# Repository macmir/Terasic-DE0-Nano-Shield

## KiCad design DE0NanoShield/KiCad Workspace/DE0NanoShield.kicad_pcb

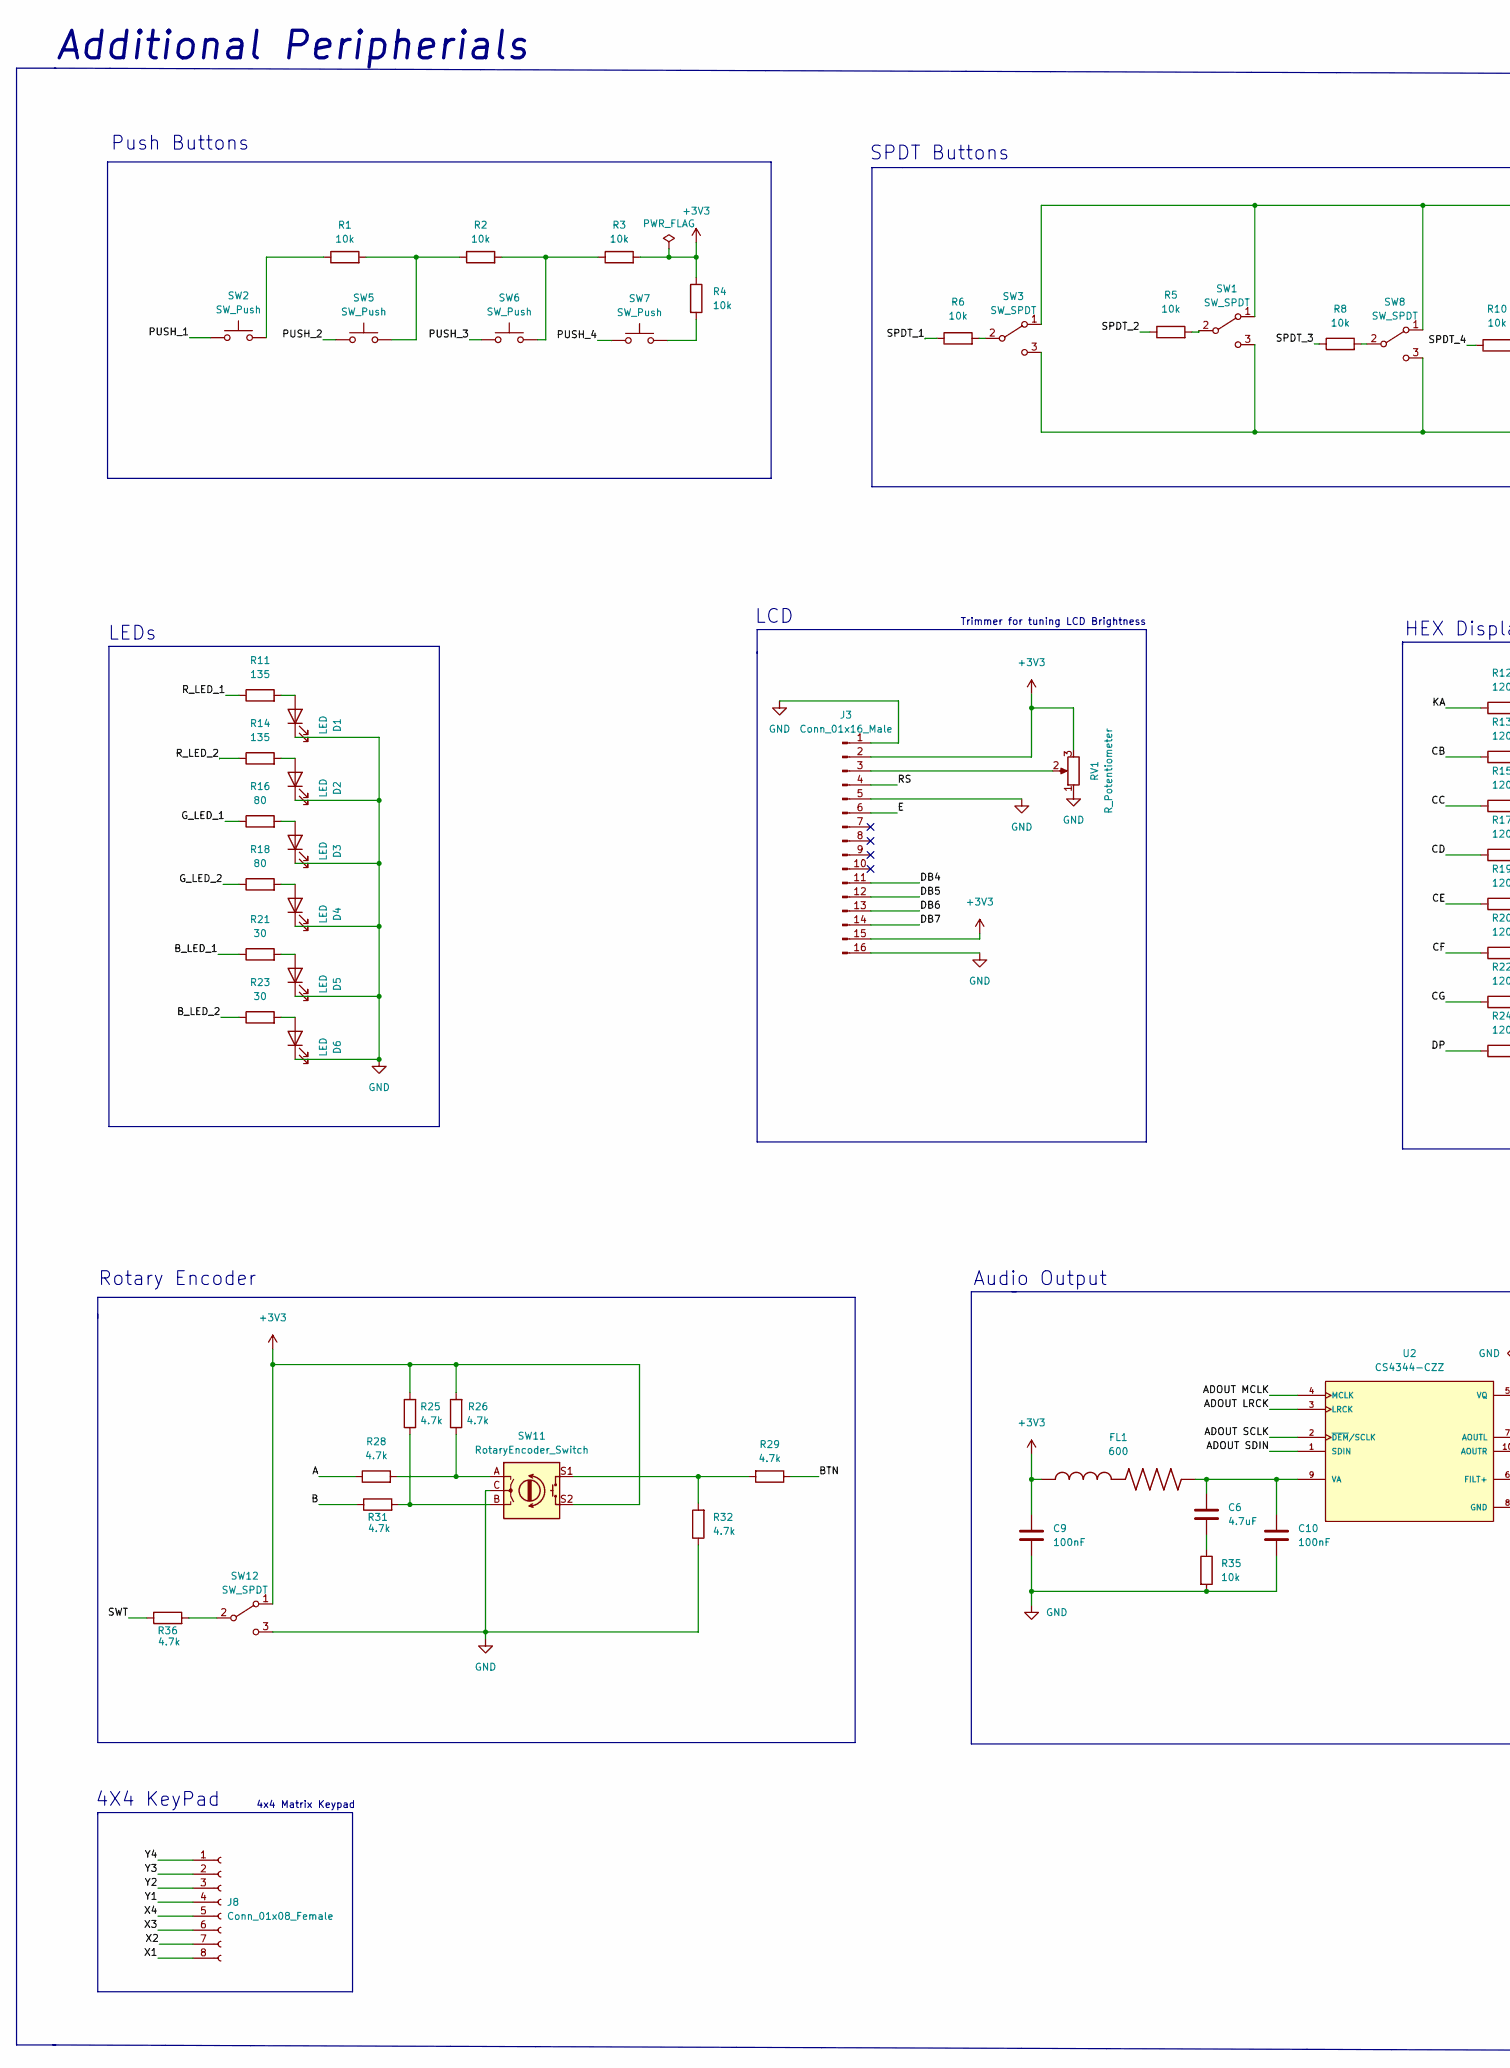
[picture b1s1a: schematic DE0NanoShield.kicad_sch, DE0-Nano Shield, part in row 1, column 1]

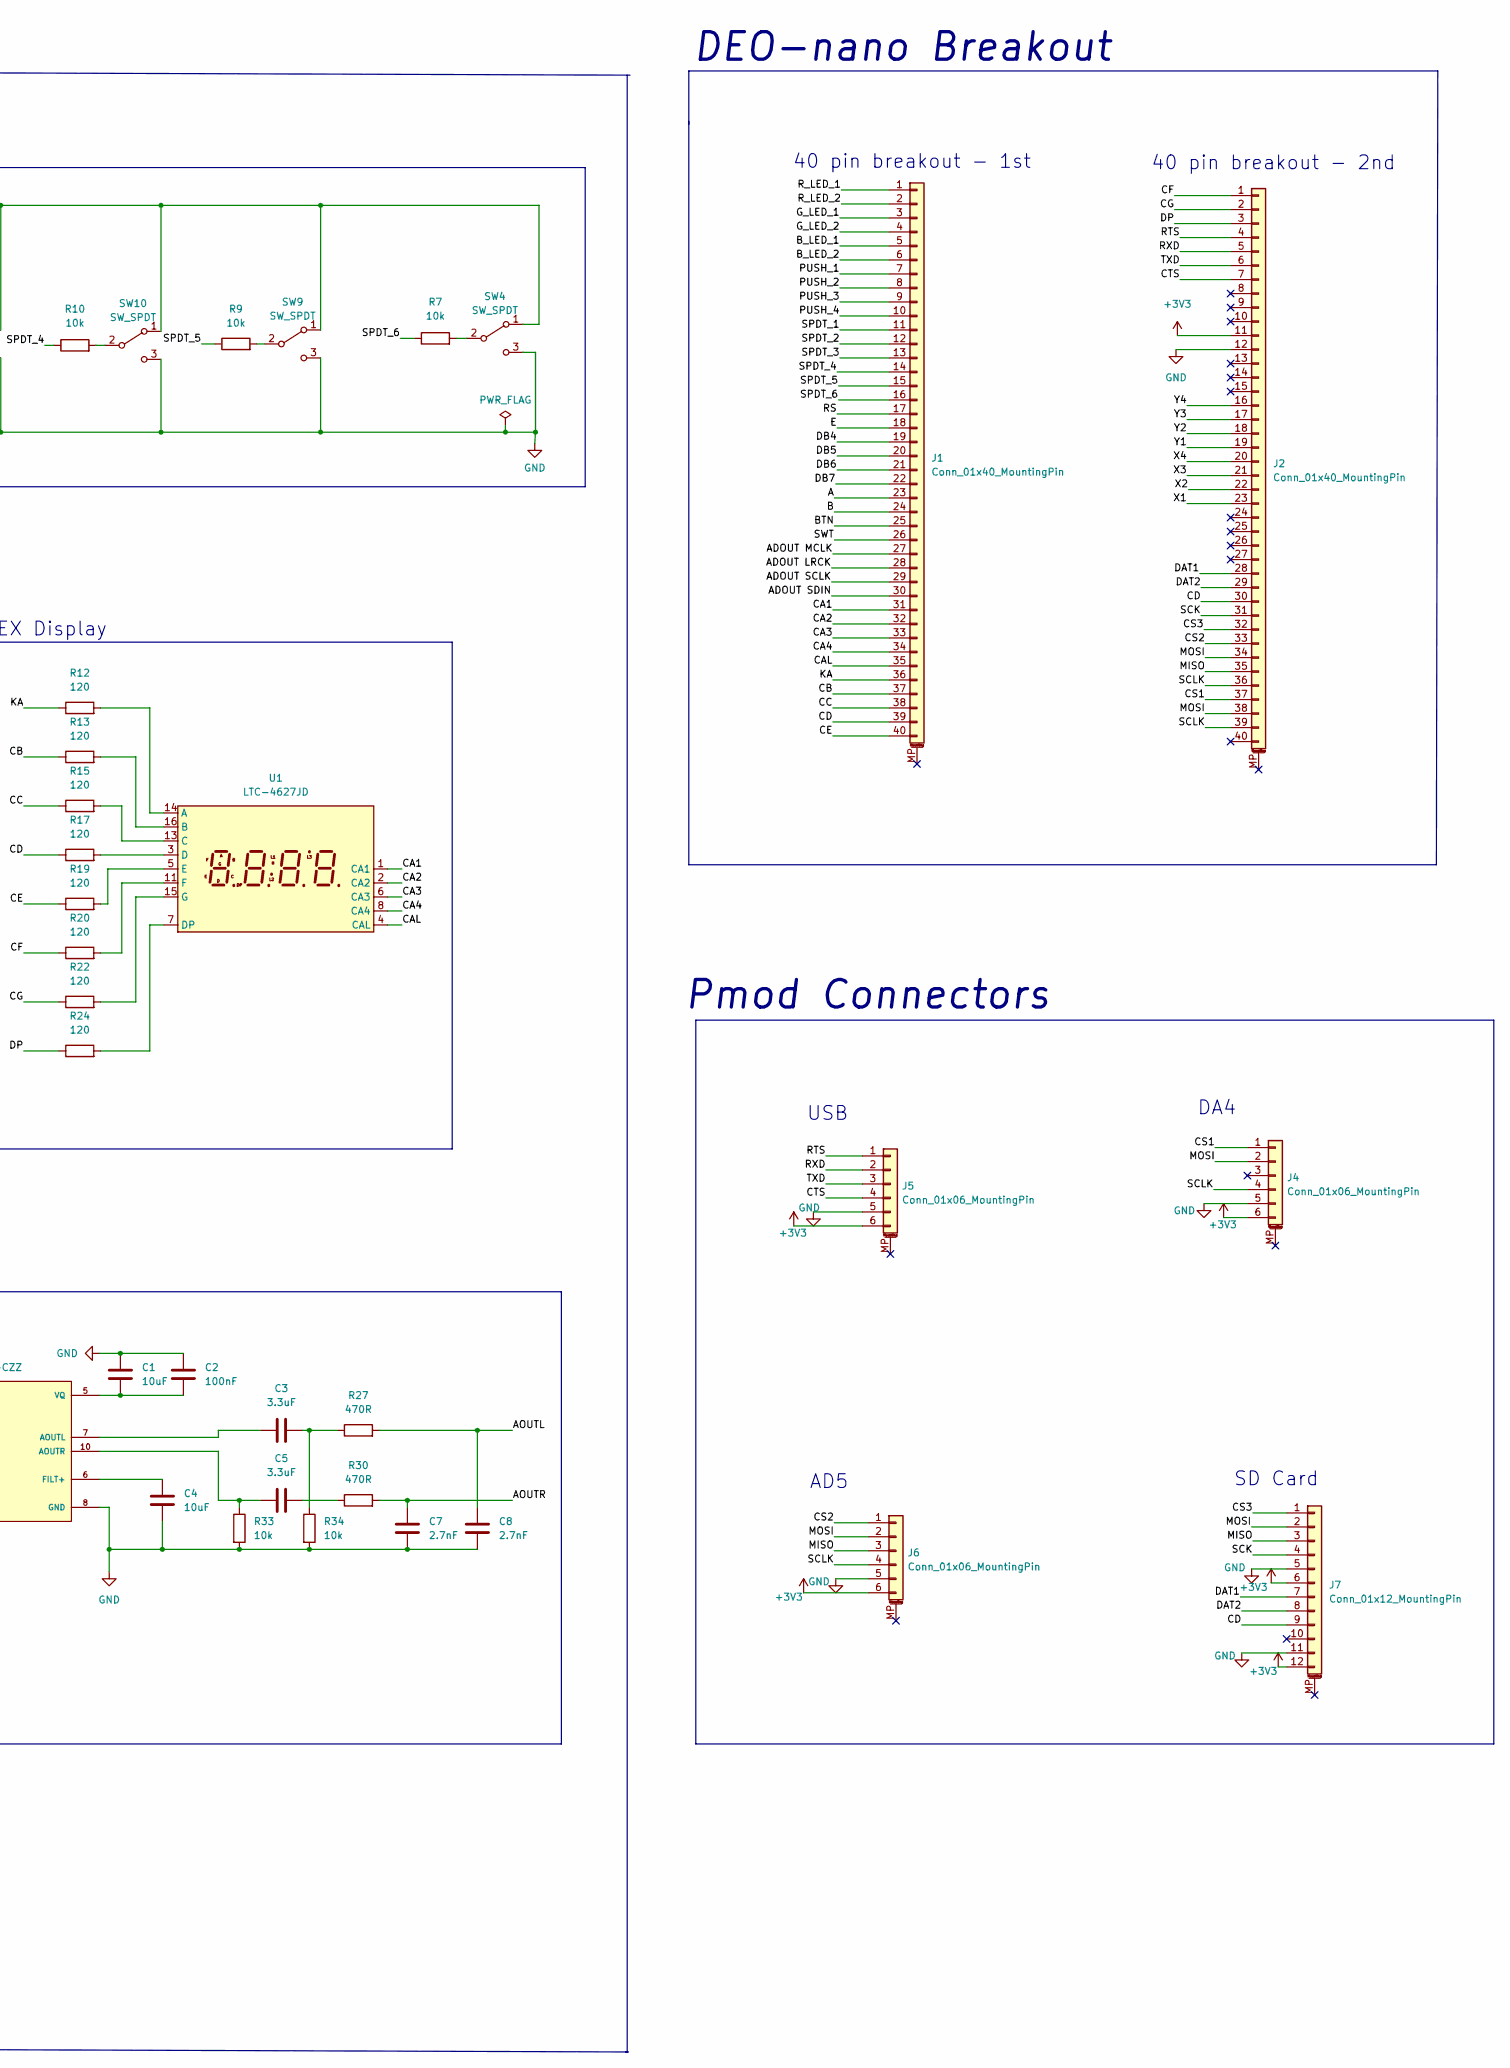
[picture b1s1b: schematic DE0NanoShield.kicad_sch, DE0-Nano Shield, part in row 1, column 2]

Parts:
C1, C4: 10uF; C_0603_1608Metric
C2, C9, C10: 100nF; C_0402_1005Metric
C3, C5: 3.3uF; C_0603_1608Metric
C6: 4.7uF; C_0603_1608Metric
C7, C8: 2.7nF; C_0402_1005Metric
D1, D2, D3, D4, D5, D6: LED; LED_0603_1608Metric
FL1: 600; BEADC1005X55N
J1, J2: Conn_01x40_MountingPin; Hirose_FH12-40S-0.5SH_1x40-1MP_P0.50mm_Horizontal
J3: Conn_01x16_Male; JST_PH_B16B-PH-K_1x16_P2.00mm_Vertical
J4, J5, J6: Conn_01x06_MountingPin; JST_GH_SM06B-GHS-TB_1x06-1MP_P1.25mm_Horizontal
J7: Conn_01x12_MountingPin; JST_GH_SM12B-GHS-TB_1x12-1MP_P1.25mm_Horizontal
J8: Conn_01x08_Female; JST_EH_B8B-EH-A_1x08_P2.50mm_Vertical
R1, R2, R3, R4, R5, R6, R7, R8, R9, R10, R35: 10k; R_0603_1608Metric
R11, R14: 135; R_0402_1005Metric
R12, R13, R15, R17, R19, R20, R22, R24: 120; R_0402_1005Metric
R16, R18: 80; R_0402_1005Metric
R21, R23: 30; R_0402_1005Metric
R25, R26, R28, R29, R31, R32, R36: 4.7k; R_0603_1608Metric
R27: 470R; R_0603_1608Metric
R30: 470R; R_0402_1005Metric
R33, R34: 10k; R_0612_1632Metric
RV1: R_Potentiometer; Potentiometer_Bourns_3224W_Vertical
SW1, SW3, SW4, SW8, SW9, SW10, SW12: SW_SPDT; SW_SPDT_PCM12
SW2, SW5, SW6, SW7: SW_Push; SW_Push_SPST_NO_Alps_SKRK
SW11: RotaryEncoder_Switch; RotaryEncoder_Alps_EC11E-Switch_Vertical_H20mm
U1: LTC-4627JD; LTC-4627Jx
U2: CS4344-CZZ; SOP50P490X110-10N; PARTREV F2

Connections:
+3V3: C9.1, FL1.1, J2.11, J3.2, J3.15, J4.6, J5.6, J6.6, J7.6, J7.12, R3.2, R4.1, R25.2, R26.2, RV1.3, SW11.S2, SW12.1 (A)
/A: J1.23, R28.1
/ADOUT LRCK: J1.28, U2.3 (LRCK)
/ADOUT MCLK: J1.27, U2.4 (MCLK)
/ADOUT SCLK: J1.29, U2.2 (~DEM/SCLK)
/ADOUT SDIN: J1.30, U2.1 (SDIN)
/AOUTL: C8.1, R27.2
/AOUTR: C7.1, R30.2
/B: J1.24, R31.1
/BTN: J1.25, R29.1
/B_LED_1: J1.5, R21.1
/B_LED_2: J1.6, R23.1
/CA1: J1.31, U1.1 (CA1)
/CA2: J1.32, U1.2 (CA2)
/CA3: J1.33, U1.6 (CA3)
/CA4: J1.34, U1.8 (CA4)
/CAL: J1.35, U1.4 (CAL)
/CB: J1.37, R13.1
/CC: J1.38, R15.1
/CD: J1.39, J2.30, J7.9, R17.1
/CE: J1.40, R19.1
/CF: J2.1, R20.1
/CG: J2.2, R22.1
/CS1: J2.37, J4.1
/CS2: J2.33, J6.1
/CS3: J2.32, J7.1
/CTS: J2.7, J5.4
/DAT1: J2.28, J7.7
/DAT2: J2.29, J7.8
/DB4: J1.19, J3.11
/DB5: J1.20, J3.12
/DB6: J1.21, J3.13
/DB7: J1.22, J3.14
/DP: J2.3, R24.1
/E: J1.18, J3.6
/G_LED_1: J1.3, R16.1
/G_LED_2: J1.4, R18.1
/KA: J1.36, R12.1
/MISO: J2.35, J6.3, J7.3
/MOSI: J2.34, J2.38, J4.2, J6.2, J7.2
/PUSH_1: J1.7, SW2.1
/PUSH_2: J1.8, SW5.1
/PUSH_3: J1.9, SW6.1
/PUSH_4: J1.10, SW7.1
/RS: J1.17, J3.4
/RTS: J2.4, J5.1
/RXD: J2.5, J5.2
/R_LED_1: J1.1, R11.1
/R_LED_2: J1.2, R14.1
/SCK: J2.31, J7.4
/SCLK: J2.36, J2.39, J4.4, J6.4
/SPDT_1: J1.11, R6.1
/SPDT_2: J1.12, R5.1
/SPDT_3: J1.13, R8.1
/SPDT_4: J1.14, R10.1
/SPDT_5: J1.15, R9.1
/SPDT_6: J1.16, R7.1
/SWT: J1.26, R36.1
/TXD: J2.6, J5.3
/X1: J2.23, J8.8
/X2: J2.22, J8.7
/X3: J2.21, J8.6
/X4: J2.20, J8.5
/Y1: J2.19, J8.4
/Y2: J2.18, J8.3
/Y3: J2.17, J8.2
/Y4: J2.16, J8.1
GND: C1.1, C2.1, C4.2, C7.2, C8.2, C9.2, C10.2, D1.1 (K), D2.1 (K), D3.1 (K), D4.1 (K), D5.1 (K), D6.1 (K), J2.12, J3.1, J3.5, J3.16, J4.5, J5.5, J6.5, J7.5, J7.11, R32.1, R33.2, R34.2, R35.2, RV1.1, SW1.3 (C), SW3.3 (C), SW4.3 (C), SW8.3 (C), SW9.3 (C), SW10.3 (C), SW11.C, SW12.3 (C), U2.8 (GND)
unnamed: C1.2, C2.2, U2.5 (VQ)
unnamed: C3.1, R27.1, R34.1
unnamed: C3.2, U2.7 (AOUTL)
unnamed: C4.1, U2.6 (FILT+)
unnamed: C5.1, R30.1
unnamed: C5.2, R33.1, U2.10 (AOUTR)
unnamed: C6.2, R35.1
unnamed: C6.1, C10.1, FL1.2, U2.9 (VA)
unnamed: D1.2 (A), R11.2
unnamed: D2.2 (A), R14.2
unnamed: D3.2 (A), R16.2
unnamed: D4.2 (A), R18.2
unnamed: D5.2 (A), R21.2
unnamed: D6.2 (A), R23.2
unnamed: J3.3, RV1.2
unnamed: R1.1, SW2.2
unnamed: R1.2, R2.1, SW5.2
unnamed: R2.2, R3.1, SW6.2
unnamed: R4.2, SW7.2
unnamed: R5.2, SW1.2 (B)
unnamed: R6.2, SW3.2 (B)
unnamed: R7.2, SW4.2 (B)
unnamed: R8.2, SW8.2 (B)
unnamed: R9.2, SW9.2 (B)
unnamed: R10.2, SW10.2 (B)
unnamed: R12.2, U1.14 (A)
unnamed: R13.2, U1.16 (B)
unnamed: R15.2, U1.13 (C)
unnamed: R17.2, U1.3 (D)
unnamed: R19.2, U1.5 (E)
unnamed: R20.2, U1.11 (F)
unnamed: R22.2, U1.15 (G)
unnamed: R24.2, U1.7 (DP)
unnamed: R25.1, R31.2, SW11.B
unnamed: R26.1, R28.2, SW11.A
unnamed: R29.2, R32.2, SW11.S1
unnamed: R36.2, SW12.2 (B)
unnamed: SW1.1 (A), SW3.1 (A), SW4.1 (A), SW8.1 (A), SW9.1 (A), SW10.1 (A)

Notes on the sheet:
Audio Output
DEO-nano Breakout
Rotary Encoder
4X4 KeyPad
Trimmer for tuning LCD Brightness
USB
40 pin breakout - 2nd
AD5
40 pin breakout - 1st
SD Card
DA4
4x4 Matrix Keypad
SPDT Buttons
Pmod Connectors
LCD
Additional Peripherials
LEDs
HEX Display
Push Buttons

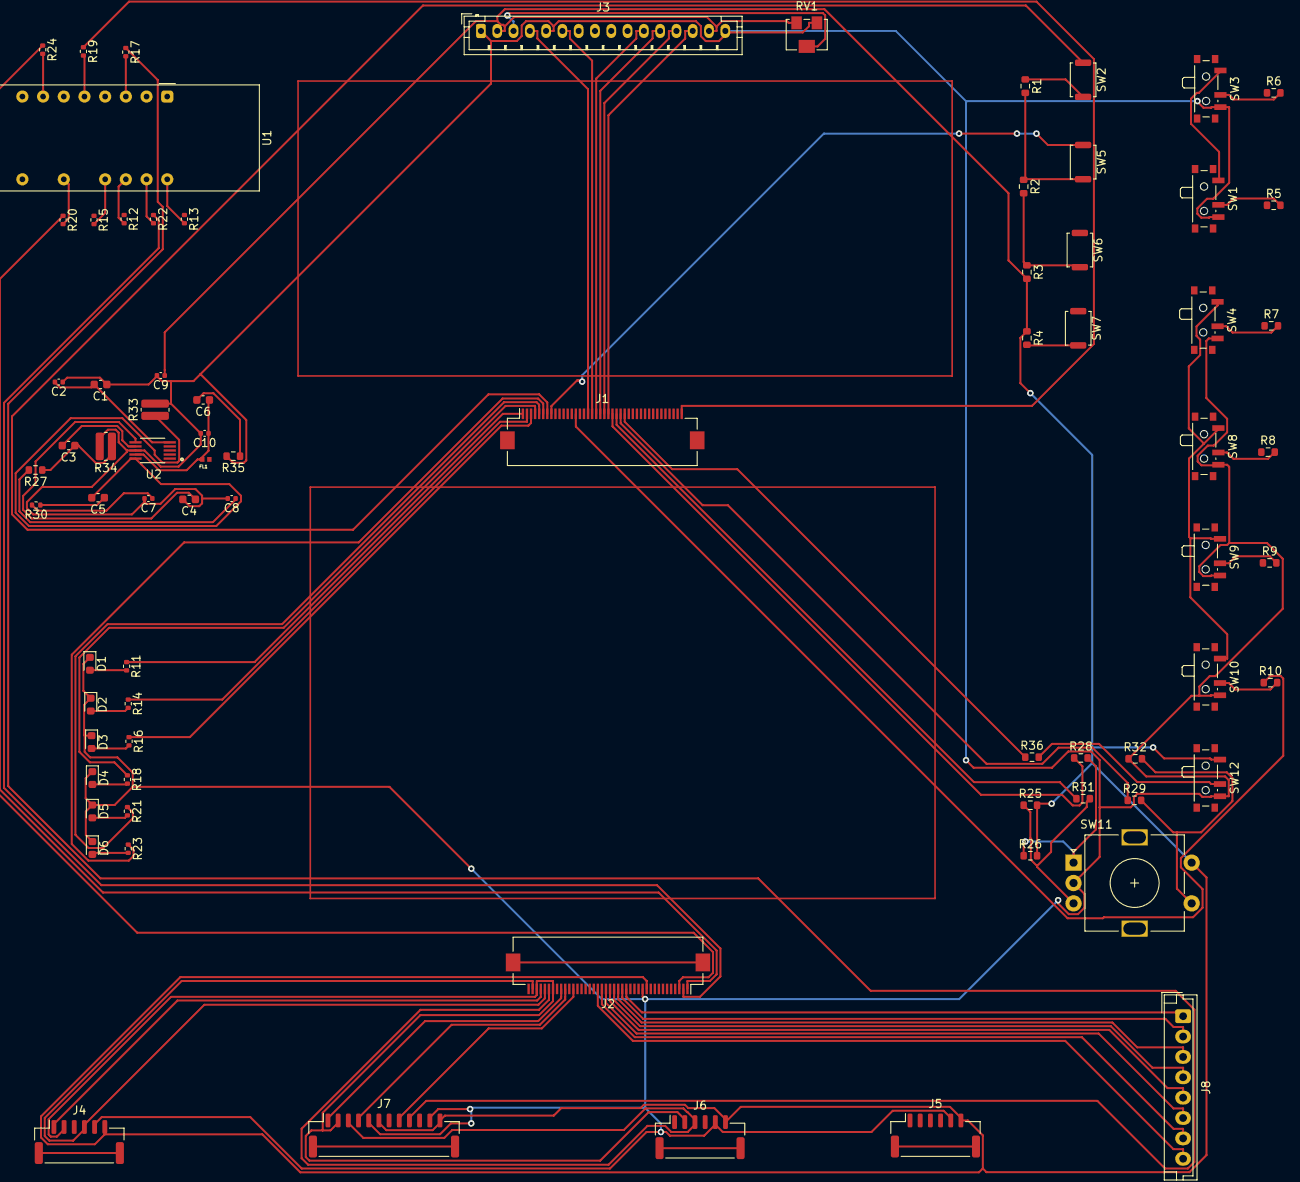
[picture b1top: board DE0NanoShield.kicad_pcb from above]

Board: 2 copper layers, 76 parts (0 on the bottom side), 106 nets.

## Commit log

2022-04-29 kicad workspace
2022-04-29 switches added
2022-04-29 rearrangement
2022-04-29 test
2022-04-29 test2
2022-04-29 new components
2022-04-29 Added footprint and symbol for hex
2022-04-29 summary
2022-04-29 added more symbols
2022-05-05 added switches and leds schematic
2022-05-18 Encoder and LCD connections
2022-05-18 Added CS4344-CZZ symbol and footprint
2022-05-19 Added audio circuit
2022-05-19 Added audio DAC circuit
2022-05-19 Added labels for audio circuits
2022-05-19 connector net labels added
2022-05-19 Added hex display circuit
2022-05-19 added pmod connections
2022-05-22 annotated schematic and added footprints
2022-05-22 Added missing footprints
2022-06-17 finished schematic completely all footprints assigned
2022-06-17 pcb layout and basic routing
